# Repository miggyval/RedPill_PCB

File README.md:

This is a repository for the RedPill KiCAD project by Miguel Valencia

[Link to BOM](https://html-preview.github.io/?url=https://github.com/miggyval/RedPill_PCB/blob/main/RedPill_Rev1.2/bom/ibom.html)

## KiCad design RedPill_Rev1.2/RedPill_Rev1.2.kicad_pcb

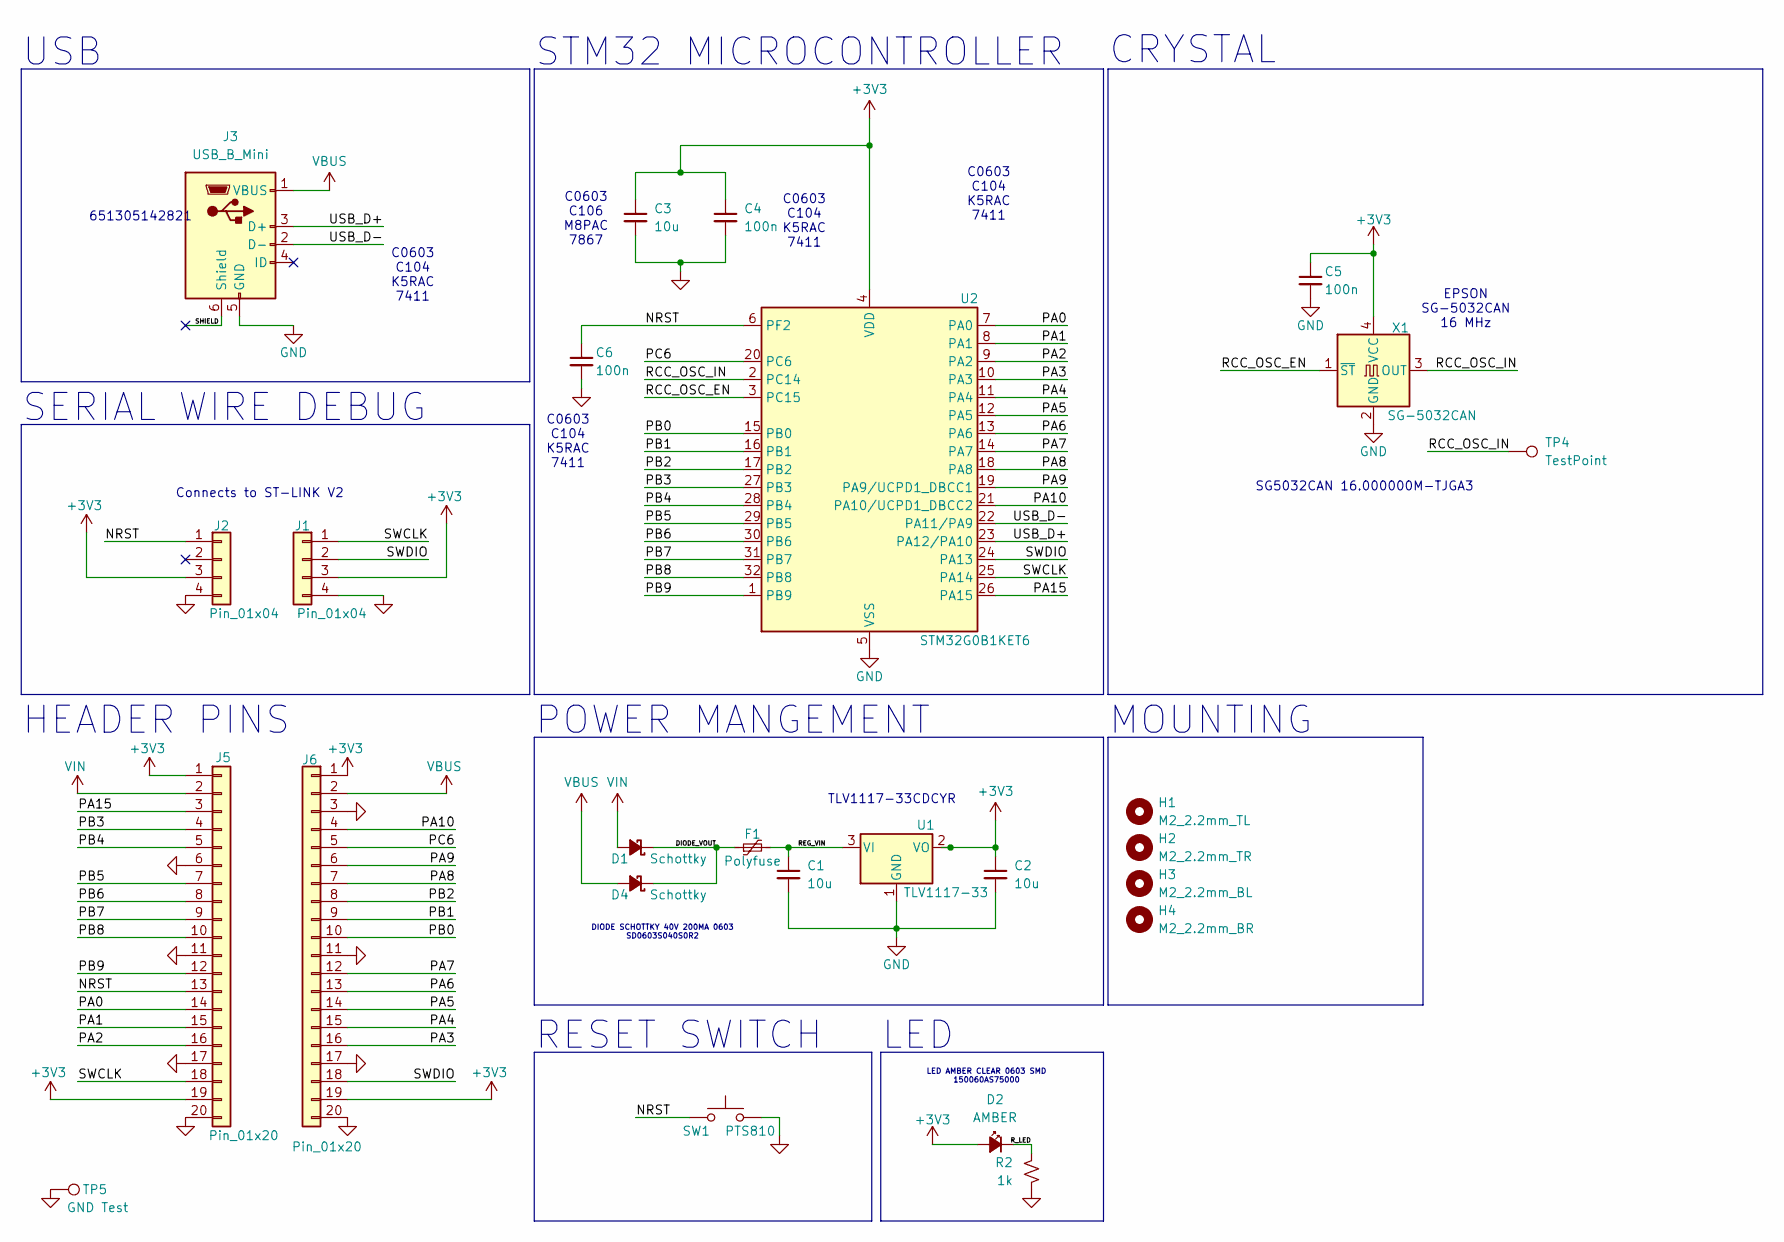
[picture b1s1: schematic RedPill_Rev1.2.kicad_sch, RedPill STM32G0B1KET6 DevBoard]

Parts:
C1, C2, C3: 10u; C_0603_1608Metric_Pad1.08x0.95mm_HandSolder
C4, C5, C6: 100n; C_0603_1608Metric_Pad1.08x0.95mm_HandSolder
D1, D4: Schottky; D_0603_1608Metric
D2: AMBER; LED_0603_1608Metric_Pad1.05x0.95mm_HandSolder
F1: Polyfuse; Fuse_1206_3216Metric
H1: M2_2.2mm_TL; MountingHole_2.2mm_M2
H2: M2_2.2mm_TR; MountingHole_2.2mm_M2
H3: M2_2.2mm_BL; MountingHole_2.2mm_M2
H4: M2_2.2mm_BR; MountingHole_2.2mm_M2
J1, J2: Pin_01x04; PinHeader_1x04_P2.54mm_Vertical
J3: USB_B_Mini; USB_Mini-B_Wuerth_65100516121_Horizontal
J5, J6: Pin_01x20; PinHeader_1x20_P2.54mm_Vertical
R2: 1k; R_0603_1608Metric_Pad0.98x0.95mm_HandSolder
SW1: PTS810; SW_SPST_PTS810
TP4: TestPoint; TestPoint_THTPad_D1.0mm_Drill0.5mm
TP5: GND Test; TestPoint_THTPad_D4.0mm_Drill2.0mm
U1: TLV1117-33; SOT-223-3_TabPin2
U2: STM32G0B1KET6; LQFP-32_7x7mm_P0.8mm
X1: SG-5032CAN; Oscillator_SMD_SeikoEpson_SG8002LB-4Pin_5.0x3.2mm

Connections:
+3V3: C2.1, C3.1, C4.1, C5.1, D2.2 (A), J1.3, J2.3, J5.1, J5.19, J6.1, J6.19, U1.2 (VO), U2.4 (VDD), X1.4 (VCC)
/DIODE_VOUT: D1.1 (K), D4.1 (K), F1.1
/NRST: C6.1, J2.1, J5.13, SW1.1, U2.6 (PF2)
/PA0: J5.14, U2.7 (PA0)
/PA1: J5.15, U2.8 (PA1)
/PA2: J5.16, U2.9 (PA2)
/PA3: J6.16, U2.10 (PA3)
/PA4: J6.15, U2.11 (PA4)
/PA5: J6.14, U2.12 (PA5)
/PA6: J6.13, U2.13 (PA6)
/PA7: J6.12, U2.14 (PA7)
/PA8: J6.7, U2.18 (PA8)
/PA9: J6.6, U2.19 (PA9/UCPD1_DBCC1)
/PA10: J6.4, U2.21 (PA10/UCPD1_DBCC2)
/PA15: J5.3, U2.26 (PA15)
/PB0: J6.10, U2.15 (PB0)
/PB1: J6.9, U2.16 (PB1)
/PB2: J6.8, U2.17 (PB2)
/PB3: J5.4, U2.27 (PB3)
/PB4: J5.5, U2.28 (PB4)
/PB5: J5.7, U2.29 (PB5)
/PB6: J5.8, U2.30 (PB6)
/PB7: J5.9, U2.31 (PB7)
/PB8: J5.10, U2.32 (PB8)
/PB9: J5.12, U2.1 (PB9)
/PC6: J6.5, U2.20 (PC6)
/RCC_OSC_EN: U2.3 (PC15), X1.1 (~ST)
/RCC_OSC_IN: TP4.1, U2.2 (PC14), X1.3 (OUT)
/REG_VIN: C1.1, F1.2, U1.3 (VI)
/R_LED: D2.1 (K), R2.2
/SHIELD: J3.6 (Shield), J3.7 (Shield_2), J3.8 (Shield_3), J3.9 (Shield_4)
/SWCLK: J1.1, J5.18, U2.25 (PA14)
/SWDIO: J1.2, J6.18, U2.24 (PA13)
/USB_D+: J3.3 (D+), U2.23 (PA12/PA10)
/USB_D-: J3.2 (D-), U2.22 (PA11/PA9)
GND: C1.2, C2.2, C3.2, C4.2, C5.2, C6.2, J1.4, J2.4, J3.5 (GND), J5.6, J5.11, J5.17, J5.20, J6.3, J6.11, J6.17, J6.20, R2.1, SW1.2, TP5.1, U1.1 (GND), U2.5 (VSS), X1.2 (GND)
VBUS: D4.2 (A), J3.1 (VBUS), J6.2
VIN: D1.2 (A), J5.2

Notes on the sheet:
651305142821
Connects to ST-LINK V2
MOUNTING
LED AMBER CLEAR 0603 SMD 150060AS75000
STM32 MICROCONTROLLER
SG5032CAN 16.000000M-TJGA3
SERIAL WIRE DEBUG
DIODE SCHOTTKY 40V 200MA 0603 SD0603S040S0R2
EPSON SG-5032CAN 16 MHz
RESET SWITCH
USB
C0603 C104 K5RAC 7411
TLV1117-33CDCYR
CRYSTAL
HEADER PINS
POWER MANGEMENT
C0603 C106 M8PAC 7867
LED

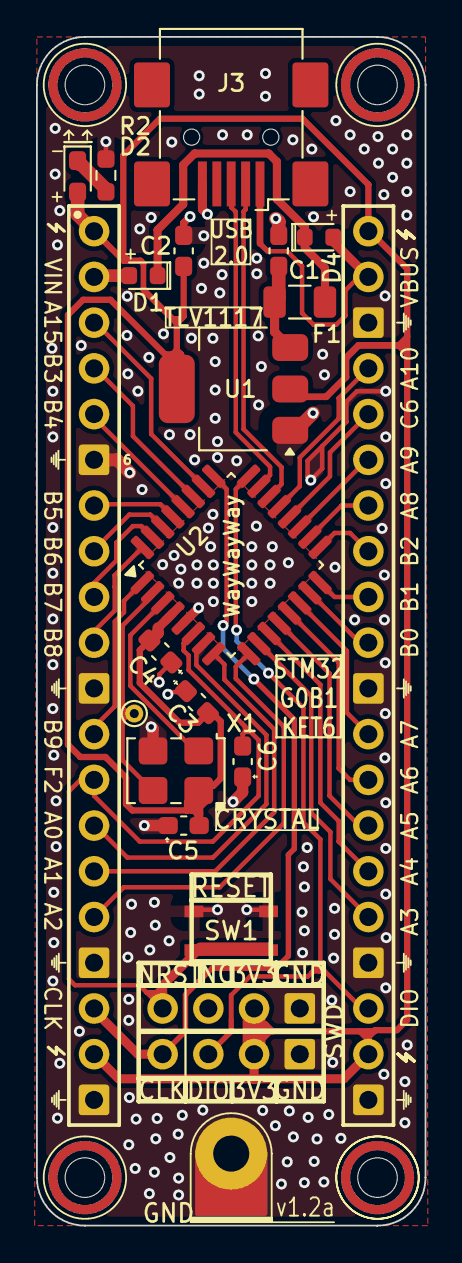
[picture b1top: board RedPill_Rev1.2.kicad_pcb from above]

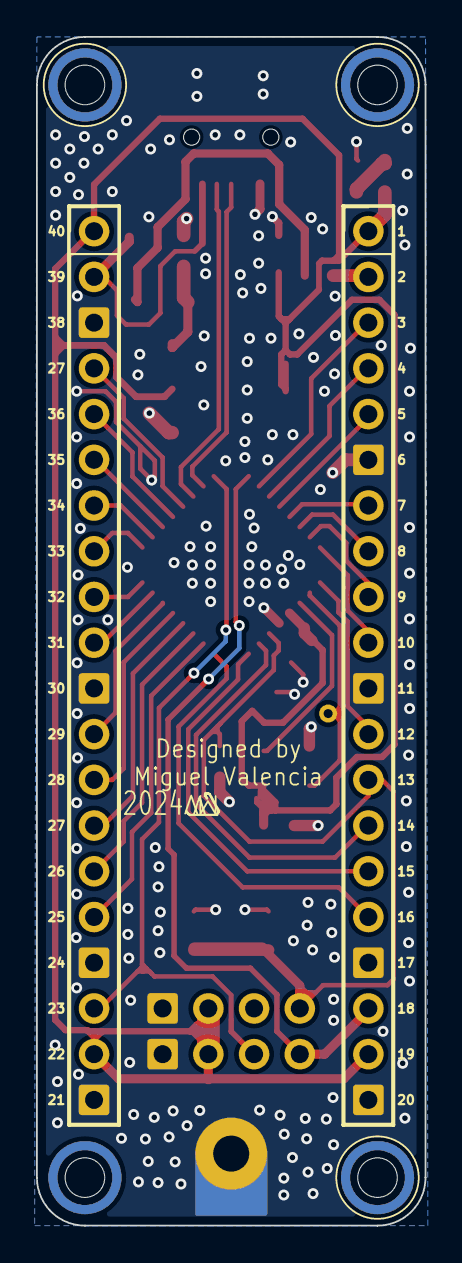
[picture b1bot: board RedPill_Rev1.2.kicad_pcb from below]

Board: 2 copper layers, 21.6 x 66.0 mm, 26 parts (6 on the bottom side), 38 nets.

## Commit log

2024-09-08 First commit for RedPill
2024-09-10 Fixed up schematic layout
2024-09-10 Added BOM
2024-09-17 Added USB-C
2024-09-27 Made silkscreen pretty
2024-09-27 v1.2a
